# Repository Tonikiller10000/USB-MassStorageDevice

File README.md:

# USB MassStorageDevice

This project is an USB mass storage made with:
- 2x K9GAG08U0E 16GB NAND flash memory chips (32GB total) 
- lateral switch for read-only operation mode 
- an ST72681 memory controller 
- LD3985 3.3V regulator
- 12MHz crystal resonator
- other passive components

After testing the board with an 220nF THT ceramic capacitor because the SMD did not arrived in time, I made some improvisations trying to fix it, and
 it still `does not work`. It seems like the memory chip and the controller ic\`s are not compatible so 
 `I will have another look on this project in the distant future` with different components. I am looking into STM32 specs and usb 3.0 to SDMMC DMA transfer
 including some software functions with hardware interaction sounds verry intheresting. And cheaper.

Schematic:

<table>
  <tr>
    <td></td>
    <td></td>
    <td></td>
  </tr>
 </table>

Datasheets:
- NAND: https://pdf1.alldatasheet.com/datasheet-pdf/view/104019/STMICROELECTRONICS/ST72681.html
- Controller: https://pdf1.alldatasheet.com/datasheet-pdf/view/1134995/SAMSUNG/K9GAG08U0E.html
- Regulator: https://pdf1.alldatasheet.com/datasheet-pdf/view/85490/STMICROELECTRONICS/LD3985.html

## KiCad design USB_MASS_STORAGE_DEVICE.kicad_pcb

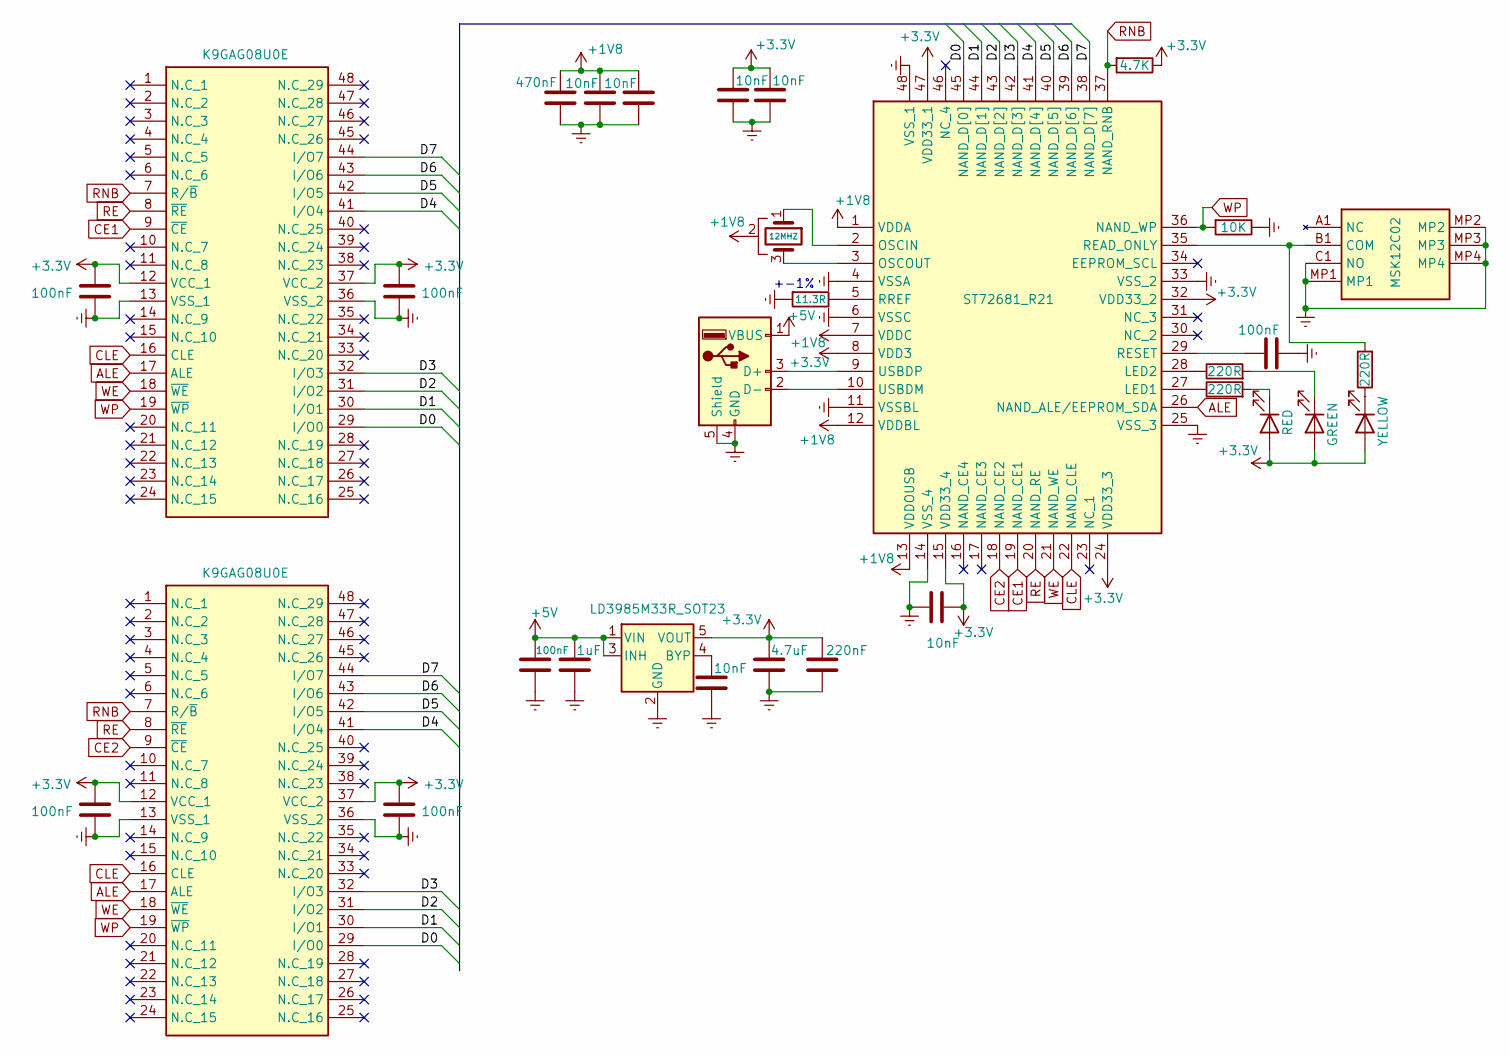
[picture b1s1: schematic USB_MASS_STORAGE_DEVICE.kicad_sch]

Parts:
C1, C2, C3, C5, C6, C14: 100nF; C_0805_2012Metric
C4, C10, C11, C13, C16, C17: 10nF; C_0805_2012Metric
C7: 470nF; C_0805_2012Metric
C8: 1uF; C_0805_2012Metric
C12: 4.7uF; C_0805_2012Metric
C19: 220nF; C_0805_2012Metric
D1: RED; LED_PLCC_2835
D2: GREEN; LED_PLCC_2835
D3: YELLOW; LED_PLCC_2835
J1: USB_A; USB_A_CNCTech_1001-011-01101_Horizontal
R1, R2, R7: 220R; R_1206_3216Metric
R3: 10K; R_1206_3216Metric
R4: 11.3R; R_1206_3216Metric
R5: 4.7K; R_1206_3216Metric
SW1: MSK12C02; Manufacturer_Part_Number MSK12C02
U1: LD3985M33R_SOT23; SOT-23-5
Y2: 12MHZ; Resonator_SMD_Murata_CSTxExxV-3Pin_3.0x1.1mm
f1: ST72681_R21; QFP50P900X900X160-48N; Manufacturer_Part_Number ST72681/R21; Mouser Part Number N/A
m1, m2: K9GAG08U0E; SOP50P2000X120-48N; Manufacturer_Part_Number K9GAG08U0E

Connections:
+1V8: C7.2, C10.2, C13.2, Y2.2, f1.1 (VDDA), f1.7 (VDDC), f1.12 (VDDBL), f1.13 (VDDOUSB)
+3V3: C1.2, C2.2, C3.2, C4.1, C6.2, C12.2, C16.2, C17.2, C19.2, D1.2 (A), D2.2 (A), D3.2 (A), R5.1, U1.5 (VOUT), f1.8 (VDD3), f1.15 (VDD33_4), f1.24 (VDD33_3), f1.32 (VDD33_2), f1.47 (VDD33_1), m1.12 (VCC_1), m1.37 (VCC_2), m2.12 (VCC_1), m2.37 (VCC_2)
+5V: C5.2, C8.2, J1.1 (VBUS), U1.1 (VIN), U1.3 (INH)
/D0: f1.45 (NAND_D[0]), m1.29 (I/O0), m2.29 (I/O0)
/D1: f1.44 (NAND_D[1]), m1.30 (I/O1), m2.30 (I/O1)
/D2: f1.43 (NAND_D[2]), m1.31 (I/O2), m2.31 (I/O2)
/D3: f1.42 (NAND_D[3]), m1.32 (I/O3), m2.32 (I/O3)
/D4: f1.41 (NAND_D[4]), m1.41 (I/O4), m2.41 (I/O4)
/D5: f1.40 (NAND_D[5]), m1.42 (I/O5), m2.42 (I/O5)
/D6: f1.39 (NAND_D[6]), m1.43 (I/O6), m2.43 (I/O6)
/D7: f1.38 (NAND_D[7]), m1.44 (I/O7), m2.44 (I/O7)
ALE: f1.26 (NAND_ALE/EEPROM_SDA), m1.17 (ALE), m2.17 (ALE)
CE1: f1.19 (NAND_CE1), m1.9 (~CE)
CE2: f1.18 (NAND_CE2), m2.9 (~CE)
CLE: f1.22 (NAND_CLE), m1.16 (CLE), m2.16 (CLE)
Earth: C1.1, C2.1, C3.1, C4.2, C5.1, C6.1, C7.1, C8.1, C10.1, C11.1, C12.1, C13.1, C14.2, C16.1, C17.1, C19.1, J1.4 (GND), J1.5 (Shield), R3.1, R4.2, SW1.C1 (NO), SW1.MP1, SW1.MP2, SW1.MP3, SW1.MP4, U1.2 (GND), f1.4 (VSSA), f1.6 (VSSC), f1.11 (VSSBL), f1.14 (VSS_4), f1.25 (VSS_3), f1.33 (VSS_2), f1.48 (VSS_1), m1.13 (VSS_1), m1.36 (VSS_2), m2.13 (VSS_1), m2.36 (VSS_2)
unnamed: C11.2, U1.4 (BYP)
unnamed: C14.1, f1.29 (RESET)
unnamed: J1.2 (D-), f1.10 (USBDM)
unnamed: J1.3 (D+), f1.9 (USBDP)
unnamed: R1.1, f1.28 (LED2)
unnamed: D2.1 (K), R1.2
unnamed: R2.1, f1.27 (LED1)
unnamed: D1.1 (K), R2.2
unnamed: R4.1, f1.5 (RREF)
unnamed: D3.1 (K), R7.1
unnamed: R7.2, SW1.B1 (COM), f1.35 (READ_ONLY)
unnamed: Y2.1, f1.2 (OSCIN)
unnamed: Y2.3, f1.3 (OSCOUT)
RE: f1.20 (NAND_RE), m1.8 (~RE), m2.8 (~RE)
RNB: R5.2, f1.37 (NAND_RNB), m1.7 (R/~B), m2.7 (R/~B)
WE: f1.21 (NAND_WE), m1.18 (~WE), m2.18 (~WE)
WP: R3.2, f1.36 (NAND_WP), m1.19 (~WP), m2.19 (~WP)

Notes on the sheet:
+-1%

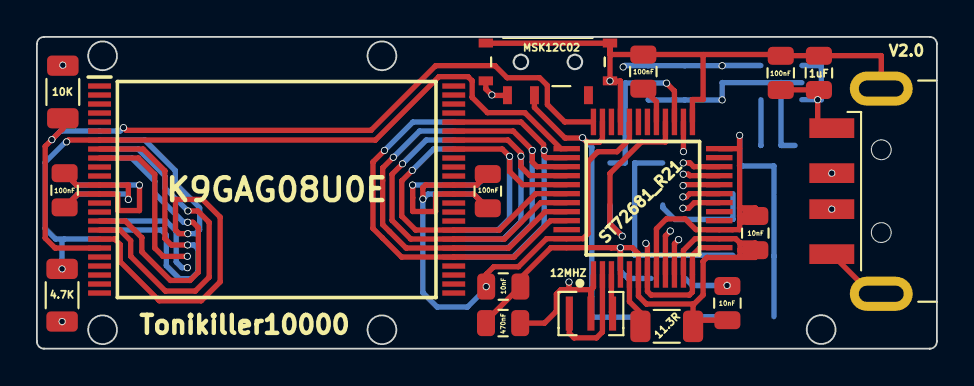
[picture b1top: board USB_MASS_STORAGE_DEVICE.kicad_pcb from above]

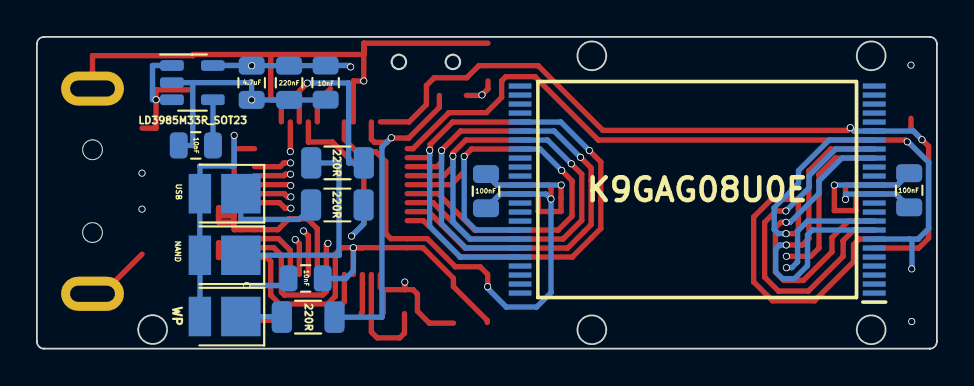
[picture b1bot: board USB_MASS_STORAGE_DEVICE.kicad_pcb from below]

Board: 4 copper layers, 50.0 x 17.3 mm, 32 parts (15 on the bottom side), 33 nets.

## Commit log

2023-09-09 The files
    I added the project files.
    The project will recive some updates next month.
2023-12-06 Abandon project
    over 30$ loss, another try maybe in few years. The controler with NAND`s are not compatible. more will be sayd in README file in the near future.
2023-12-19 firest picture
2023-12-19 pictures2
2023-12-21 Rename jlc2.jpg to JLC2.jpg
